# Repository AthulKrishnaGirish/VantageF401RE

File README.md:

# VantageF401RE

### STM32F401RE Evaluation & Development Board

**Mixed Traces PCB Design Competition — 2026  —**
**Submission by, Athul Krishna Girish**

---

## Project Overview

**VantageF401RE** is an independently designed, compact **2-layer STM32F401RE-based evaluation and development board** developed in KiCad as part of the **Mixed Traces PCB Design Competition 2026**.

The board is built around the **STM32F401RET6** microcontroller and integrates the essential features expected from a development board, including regulated power, USB connectivity, SWD programming/debugging, UART, SPI, I²C, GPIO expansion, reset and boot control, user indicators, and supporting protection and decoupling circuitry.

The design was developed independently with the **STM32 NUCLEO-F401RE** used as a functional and architectural reference. The VantageF401RE schematic, component arrangement, PCB placement, and routing were independently developed and are not a direct copy of the NUCLEO PCB layout.

---

## Project Status

### Completed — Final Design

The VantageF401RE schematic and PCB layout have been completed in KiCad.

The project includes:

- Complete STM32F401RET6-based schematic
- Power supply and 3.3 V regulation
- USB-C power and USB 2.0 interface
- USB ESD protection
- SWD programming/debugging interface
- UART interface
- SPI interface
- I²C interface
- GPIO expansion
- Reset and BOOT selection circuitry
- User button and LED
- Power and USB status indicators
- External 5 V input
- Crystal oscillator
- MCU power decoupling
- Test points
- Two-layer PCB layout
- Ground copper zones
- ERC and DRC verification
- Final Gerber and drill file generation
- Final component list and design documentation

The final PCB design achieved **0 reported DRC errors**, and the final manufacturing files were generated from the completed PCB layout.

> **Note:** The project was developed and verified as a PCB design in KiCad. No physical fabrication or hardware testing is claimed as part of this submission.

---

## Key Specifications

| Parameter | Specification |
|---|---|
| **Board Name** | VantageF401RE |
| **MCU** | STM32F401RET6 |
| **MCU Package** | LQFP-64 |
| **PCB Layers** | 2 copper layers |
| **PCB Dimensions** | 80 mm × 60 mm |
| **Design Software** | KiCad |
| **Logic Supply** | 3.3 V |
| **USB Interface** | USB Type-C / USB 2.0 |
| **Programming & Debugging** | SWD |
| **Communication Interfaces** | UART, SPI, I²C |
| **GPIO Expansion** | 20-pin header |
| **External Power** | 5 V input |
| **PCB Verification** | ERC / DRC |
| **Fabrication Requirement** | Not required |

---

## Main Features

### 1. STM32F401RET6 Core

The board uses the **STM32F401RET6**, a 64-pin LQFP STM32F4-series microcontroller.

The MCU section includes:

- 3.3 V digital supply
- Analog supply connection
- VCAP capacitor
- Local decoupling capacitors
- External HSE crystal
- Reset circuitry
- BOOT0 configuration
- SWD programming/debugging access

---

### 2. Power Supply

The board provides a regulated **3.3 V supply** for the STM32F401RET6 and peripheral circuitry.

**Power inputs**

- USB-C 5 V input
- External 5 V input

**Regulation**

An **AP2112K-3.3 LDO regulator** converts the incoming 5 V supply to 3.3 V.

The power section includes:

- Input decoupling
- Output decoupling
- 3.3 V bulk capacitance
- Power indication
- External-input protection

An **SS14 Schottky diode** is included on the external 5 V input path for protection.

---

### 3. USB-C Interface

The board provides a USB Type-C connector for power and USB 2.0 data connectivity.

The USB section includes:

- USB-C receptacle
- USB 2.0 D+ and D− connections
- CC1 and CC2 configuration resistors
- USB ESD protection
- USB D+ and D− series resistors
- USB status indicator

The USB data path uses the STM32F401RE USB pins:

- **PA11 — USB_DM**
- **PA12 — USB_DP**

---

### 4. USB ESD Protection

A **USBLC6-2SC6** protection device is placed close to the USB connector.

The protection network is incorporated into the USB data path to provide ESD protection for the USB D+ and D− lines.

The USB signal path is organized as:

```text
USB-C
  ↓
USB D+ / D−
  ↓
USB ESD Protection
  ↓
22 Ω Series Resistors
  ↓
STM32F401RET6
```

---

### 5. SWD Programming & Debugging

A dedicated 5-pin SWD header is provided for programming and debugging the STM32F401RET6.

The interface provides:

- VCC
- SWDIO
- GND
- SWCLK
- NRST

MCU connections:

- PA13 — SWDIO
- PA14 — SWCLK
- NRST — Reset

Dedicated test points are also provided for SWDIO, SWCLK, and NRST.

---

### 6. UART Interface

A dedicated 4-pin UART header provides easy access to the serial communication interface.

| UART Signal | MCU Pin |
|---|---|
| UART_TX | PA2 |
| UART_RX | PA3 |
| VCC | +3V3 |
| GND | GND |

---

### 7. SPI Interface

A dedicated 6-pin SPI header is provided.

| SPI Signal | MCU Pin |
|---|---|
| SPI_SCK | PA5 |
| SPI_MISO | PA6 |
| SPI_MOSI | PA7 |
| SPI_CS | PA4 |
| VCC | +3V3 |
| GND | GND |

---

### 8. I²C Interface

A dedicated 4-pin I²C header is provided with external pull-up resistors.

| I²C Signal | MCU Pin |
|---|---|
| I2C_SCL | PB6 |
| I2C_SDA | PB7 |
| VCC | +3V3 |
| GND | GND |

Two 4.7 kΩ pull-up resistors are provided for the I²C lines.

---

### 9. GPIO Expansion

A dedicated 20-pin GPIO expansion header provides access to multiple STM32 GPIOs along with power and ground.

The expansion header provides access to signals including:

- PA0
- PA1
- PA8
- PA9
- PA10
- PB2
- PB10
- PC6
- PB12–PB15
- PC0–PC5
- +3V3
- GND

This provides flexibility for connecting external sensors, modules, displays, and other peripherals.

---

### 10. Reset & Boot Control

**Reset**

The NRST line includes:

- 10 kΩ pull-up resistor
- Dedicated reset pushbutton
- SWD NRST connection
- NRST test point

**Boot Selection**

BOOT0 includes:

- 10 kΩ pull-down resistor
- Dedicated BOOT selection header
- +3V3 selection capability

This allows the boot configuration of the STM32F401RET6 to be conveniently controlled.

---

## User Interface

The board includes dedicated user indicators and controls.

**User LED**

- D1 — USER_LED
- Controlled through PB0
- R3 = 330 Ω current-limiting resistor

**User Button**

- SW2 — USER_BTN
- Connected to PB1
- R4 = 10 kΩ pull-up resistor

**Power LED**

- D2 — POWER
- R9 = 1 kΩ current-limiting resistor

**USB Status LED**

- D4 — USB_STATUS
- Controlled through PB5
- R12 = 1 kΩ current-limiting resistor

---

## Clock Circuit

The MCU uses an external 8 MHz HSE crystal.

The clock section consists of:

- Y1 — 8 MHz crystal
- C2 — 18 pF
- C3 — 18 pF

The crystal and its load capacitors are placed close to the MCU to maintain a compact and controlled clock path.

---

## Decoupling & Power Integrity

Local decoupling is provided around the STM32F401RET6 and the power-supply circuitry.

The design includes:

- VDD decoupling capacitors
- VCAP capacitor
- Analog supply decoupling
- 3.3 V bulk capacitance
- LDO input and output capacitors

The final PCB placement keeps critical decoupling components close to their respective power pins and maintains short power/ground paths.

---

## PCB Design

The VantageF401RE PCB was designed as a two-layer board while maintaining the competition's maximum board-size requirement.

**Final board dimensions:** 80 mm × 60 mm

**PCB design considerations**

- Central MCU placement
- Short critical signal paths
- Dedicated power section
- USB connector at the board edge
- Accessible programming/debugging header
- Clearly grouped communication headers
- GPIO expansion access
- Local MCU decoupling
- Ground copper zones
- Organized component placement
- Practical connector accessibility
- Compact routing while maintaining design-rule compliance

The PCB layout was independently developed rather than directly reproducing the NUCLEO-F401RE PCB layout.

---

## Final Component Set

The completed design contains 47 populated component references:

| Category | Quantity |
|---|---|
| MCU | 1 |
| USB Protection | 1 |
| Voltage Regulator | 1 |
| Connectors | 8 |
| Crystal | 1 |
| Resistors | 12 |
| Capacitors | 12 |
| LEDs | 3 |
| Diode | 1 |
| Switches | 2 |
| Test Points | 5 |
| **Total** | **47** |

The complete component list is available in:
`bom/VantageF401RE_Final_Component_List.xlsx`

The component reference designators in the final documentation follow the final schematic.

---

## Verification

The design was checked using KiCad's electrical and physical design-rule verification tools.

**ERC — Electrical Rules Check**

- 0 violations
- 0 errors
- 0 warnings

**DRC — Design Rules Check**

- 0 reported DRC errors

The final Gerber and drill files were generated from the completed PCB layout after routing and design-rule verification.

---

## Repository Contents

The repository contains the complete design and supporting documentation.

```text
VantageF401RE/
│
├── bom/
│   └── VantageF401RE_Final_Component_List.xlsx
│
├── docs/
│   ├── Major Decisions.md
│   └── Initial Block Diagram.png
│
├── gerbers/
│   ├── VantageF401RE_Gerbers.zip
│   └── README.md
│
├── kicad/
│   ├── VantageF401RE.kicad_sch
│   ├── VantageF401RE.kicad_pcb
│   ├── VantageF401RE.kicad_pro
│   └── README.md
│
├── pdf/
│   ├── VantageF401RE_Final_Design_Report.pdf
│   └── README.md
│
├── results/
│   ├── ERC / DRC and validation results
│   └── README.md
│
└── README.md
```

---

### Folder Description

| [`bom/`](bom/) |
Contains the final component list and BOM-related documentation.
`VantageF401RE_Final_Component_List.xlsx` — provides the final component references, values, footprints, functions, and interface mapping.

| [`docs/`](docs/) |
Contains supporting project documentation, design information, and technical documentation associated with the development of the board.

| [`gerbers/`](gerbers/) |
Contains the final manufacturing output package.
`VantageF401RE_Gerbers.zip` — includes the final copper, solder-mask, silkscreen, paste, board-outline, and drill outputs generated from KiCad.

| [`kicad/`](kicad/) |
Contains the primary editable KiCad design files, including:

- Schematic
- PCB layout
- Supporting KiCad project files

These files represent the actual circuit and PCB implementation of VantageF401RE.

| [`pdf/`](pdf/) |
Contains the final technical design report prepared for the competition submission.
`VantageF401RE_Final_Design_Report.pdf` — provides a consolidated description of the board architecture, design decisions, implementation, verification, and final outcome.

| [`results/`](results/) |
Contains design verification and validation outputs, including ERC/DRC-related results and other relevant design-check documentation.

---

## Competition Compliance

| Requirement | VantageF401RE |
|---|---|
| STM32F401RE MCU | ✓ |
| Maximum 100 mm × 100 mm | ✓ |
| Exactly 2 copper layers | ✓ |
| Power input | ✓ |
| Voltage regulation | ✓ |
| Decoupling | ✓ |
| Power indication | ✓ |
| SWD interface | ✓ |
| Reset button | ✓ |
| User button | ✓ |
| User LED | ✓ |
| UART | ✓ |
| SPI | ✓ |
| I²C | ✓ |
| GPIO expansion | ✓ |
| USB interface | ✓ |
| ERC verification | ✓ |
| DRC verification | ✓ |
| Gerber generation | ✓ |
| Final BOM | ✓ |
| Technical documentation | ✓ |

---

## Design Philosophy

The VantageF401RE was designed with the following priorities:

- Electrical correctness
- Reliable power distribution
- Practical peripheral access
- Compact PCB organization
- Clear interface grouping
- Debugging accessibility
- Protection and robustness
- Expandability
- Manufacturing-oriented PCB design
- Clean and structured documentation

The design balances the requirements of a development board with the constraints of a compact two-layer PCB.

---

## Final Outcome

The VantageF401RE project progressed from initial architecture and component planning to a completed schematic, PCB layout, verification, and manufacturing-output generation.

The final repository provides the editable KiCad design files together with the final component list, verification results, Gerber package, and technical design report.

The result is a compact, independently developed STM32F401RE evaluation and development board intended to provide convenient access to programming, debugging, communication, GPIO expansion, USB connectivity, and basic user-interface functionality.

---

## Project Information

- **Project:** VantageF401RE
- **Board:** STM32F401RE Evaluation & Development Board
- **Competition:** Mixed Traces PCB Design Competition — 2026
- **Organizer:** Mixed Signals — Electronics Association of MEC
- **Design Tool:** KiCad
- **MCU:** STM32F401RET6
- **PCB:** 2-layer, 80 mm × 60 mm

---

## Acknowledgement

Developed as a submission for the Mixed Traces PCB Design Competition 2026, organized by Mixed Signals — Electronics Association of MEC.

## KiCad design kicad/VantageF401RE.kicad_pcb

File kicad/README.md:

# VantageF401RE — KiCad Design Files

This folder contains the complete editable **KiCad project files** for the **VantageF401RE**, a custom STM32F401RE-based evaluation and development board designed for the **Mixed Traces PCB Design Competition** by Mixed Signals, Electronics Association of MEC.

The design was developed entirely in **KiCad** as a **2-layer PCB**, with a focus on functionality, accessibility, protection, compact organization, and practical embedded-system development.

---

## Project Files

| File | Description |
|------|-------------|
| `VantageF401RE.kicad_pro` | Main KiCad project file |
| `VantageF401RE.kicad_sch` | Complete electrical schematic |
| `VantageF401RE.kicad_pcb` | Final 2-layer PCB layout |

These files can be opened and edited using KiCad.

---

## Board Specifications

| Parameter | Specification |
|-----------|---------------|
| MCU | STM32F401RET6 |
| MCU Package | LQFP-64 |
| PCB Layers | 2 |
| Board Size | 80 mm × 60 mm |
| Design Tool | KiCad |
| USB Interface | USB Type-C, USB 2.0 |
| Supply Voltage | 3.3 V regulated |
| External Input | 5 V |
| Debug Interface | SWD |
| Oscillator | 8 MHz external crystal |

The board size remains well within the competition's maximum permitted **100 mm × 100 mm** area.

---

## Main Functional Blocks

The VantageF401RE integrates the following functional sections:

### 1. STM32F401RET6 Core

The STM32F401RET6 serves as the main processing device.

The design includes:

- External 8 MHz crystal oscillator
- VCAP1 capacitor
- MCU power decoupling
- Analog supply decoupling
- Reset circuitry
- BOOT0 configuration
- Dedicated programming/debug access

---

### 2. Power Management

The power section provides a regulated 3.3 V supply for the MCU and peripherals.

Features include:

- USB-C 5 V input
- External 5 V input
- AP2112K-3.3 LDO regulator
- Input and output capacitors
- Schottky-diode protection for external 5 V input
- Power LED
- 3.3 V and GND test points

---

### 3. USB Interface

A USB-C connector is provided for USB 2.0 connectivity and 5 V power input.

The USB section includes:

- USB Type-C receptacle
- USB D+ and D− connections
- CC1 and CC2 resistors
- USB ESD protection using USBLC6-2SC6
- USB data-line series resistors
- USB status LED
- Dedicated USB 5 V power rail

The USB data path is protected before reaching the STM32 USB pins.

---

### 4. SWD Programming and Debugging

A dedicated 5-pin SWD header is provided for programming and debugging the STM32.

The interface exposes:

- VCC
- SWDIO
- GND
- SWCLK
- NRST

Test points are also provided for SWDIO, SWCLK, and NRST.

---

### 5. Reset and Boot Configuration

The board provides dedicated controls for reliable startup and debugging.

Features include:

- Hardware reset push button
- NRST pull-up resistor
- BOOT0 pull-down resistor
- BOOT selection header

---

### 6. Communication Interfaces

Dedicated headers are provided for commonly used embedded communication protocols.

#### UART

- UART TX
- UART RX
- 3.3 V
- GND

#### SPI

- SPI SCK
- SPI MISO
- SPI MOSI
- SPI CS
- 3.3 V
- GND

#### I²C

- I²C SCL
- I²C SDA
- 3.3 V
- GND
- Dedicated pull-up resistors

---

### 7. GPIO Expansion

A dedicated **2×10 GPIO header** provides convenient access to multiple STM32 GPIO pins along with power and ground connections.

This allows external sensors, displays, modules, and other peripherals to be connected directly to the board.

---

### 8. User Interface

The board includes:

- User push button
- User LED
- Reset button
- Power LED
- USB status LED
- BOOT selection header

These provide basic interaction and visual feedback during development and debugging.

---

### 9. Clock and Decoupling

The MCU clock section uses an external **8 MHz crystal oscillator** with dedicated load capacitors.

The power network includes:

- Local 100 nF MCU decoupling capacitors
- Bulk 4.7 µF decoupling
- Analog supply filtering
- VCAP1 capacitor
- Regulator input/output capacitors

The decoupling components were placed close to their respective power pins and functional blocks during PCB layout.

---

### 10. Test and Debug Access

Dedicated test points are provided for important signals:

- 3.3 V
- GND
- SWDIO
- SWCLK
- NRST

These improve accessibility for oscilloscope probing, debugging, and laboratory measurements.

---

## PCB Layout

The final PCB uses a **2-layer copper stack-up** with an **80 mm × 60 mm** board outline.

The placement was organized into functional regions, including:

- Central STM32 MCU section
- USB and power section near the board edge
- SWD/debug section
- Communication interface headers
- GPIO expansion
- Clock circuitry
- User-control section
- Power indication
- Test points

Ground planes are used to provide continuous ground-return paths and improve overall PCB organization.

The layout was routed while considering component accessibility, signal paths, power distribution, and the physical constraints of a 2-layer board.

---

## Design Verification

The final schematic and PCB were verified using KiCad's electrical and PCB design-rule checking tools.

### ERC

**Electrical Rules Check:**

- Violations: **0**
- Errors: **0**
- Warnings: **0**

### DRC

**Design Rules Check:**

- Reported violations: **0**
- Errors: **0**
- Intentional exclusions: **4**

The intentional exclusions correspond to reviewed USB-C connector mechanical hole-clearance checks associated with the selected footprint.

Detailed ERC and DRC reports are available in the repository's [`results/`](../results/) directory.

---

## Design Approach

The VantageF401RE was designed as a complete development platform rather than only an STM32 breakout board.

The design combines:

**Processing + Power + USB + Debugging + Communication + Expansion + User Interface + Protection**

within a compact 2-layer PCB.

Particular attention was given to:

- Power integrity
- Local decoupling
- USB protection
- Signal accessibility
- Debug accessibility
- Peripheral expansion
- Component placement
- Ground connectivity
- PCB manufacturability
- Design-rule compliance

---

## Related Repository Folders

The complete project is organized into dedicated sections:

### [`bom/`](../bom/)

Contains the component selection and BOM documentation.

### [`docs/`](../docs/)

Contains project documentation, including:

- Major design decisions
- Initial block diagram
- Progress evaluation documentation

### [`results/`](../results/)

Contains the final ERC and DRC verification reports.

### [`gerbers/`](../gerbers/)

Contains the final Gerber and drill files prepared for PCB fabrication.

### [`pdf/`](../pdf/)

Reserved for the final project documentation PDF.

---

## Opening the Project

To inspect or continue development:

1. Install a compatible version of KiCad.
2. Open `VantageF401RE.kicad_pro`.
3. Open the schematic through the KiCad project manager.
4. Open the PCB layout from the same project.

The `.kicad_sch` and `.kicad_pcb` files can also be opened individually when required.

---

## Final Design Status

The VantageF401RE design has completed:

- Component selection
- Schematic development
- PCB component placement
- PCB routing
- Power-system implementation
- USB interface implementation
- SWD interface implementation
- UART, SPI and I²C interfaces
- GPIO expansion
- User interface circuitry
- PCB design-rule verification
- Schematic electrical-rule verification
- Gerber and drill-file generation

The files in this directory represent the **final editable KiCad design** submitted as part of the project.

---

**Project:** VantageF401RE  
**MCU:** STM32F401RET6  
**PCB:** 2-Layer, 80 mm × 60 mm  
**EDA Tool:** KiCad  
**Status:** Final Design Completed

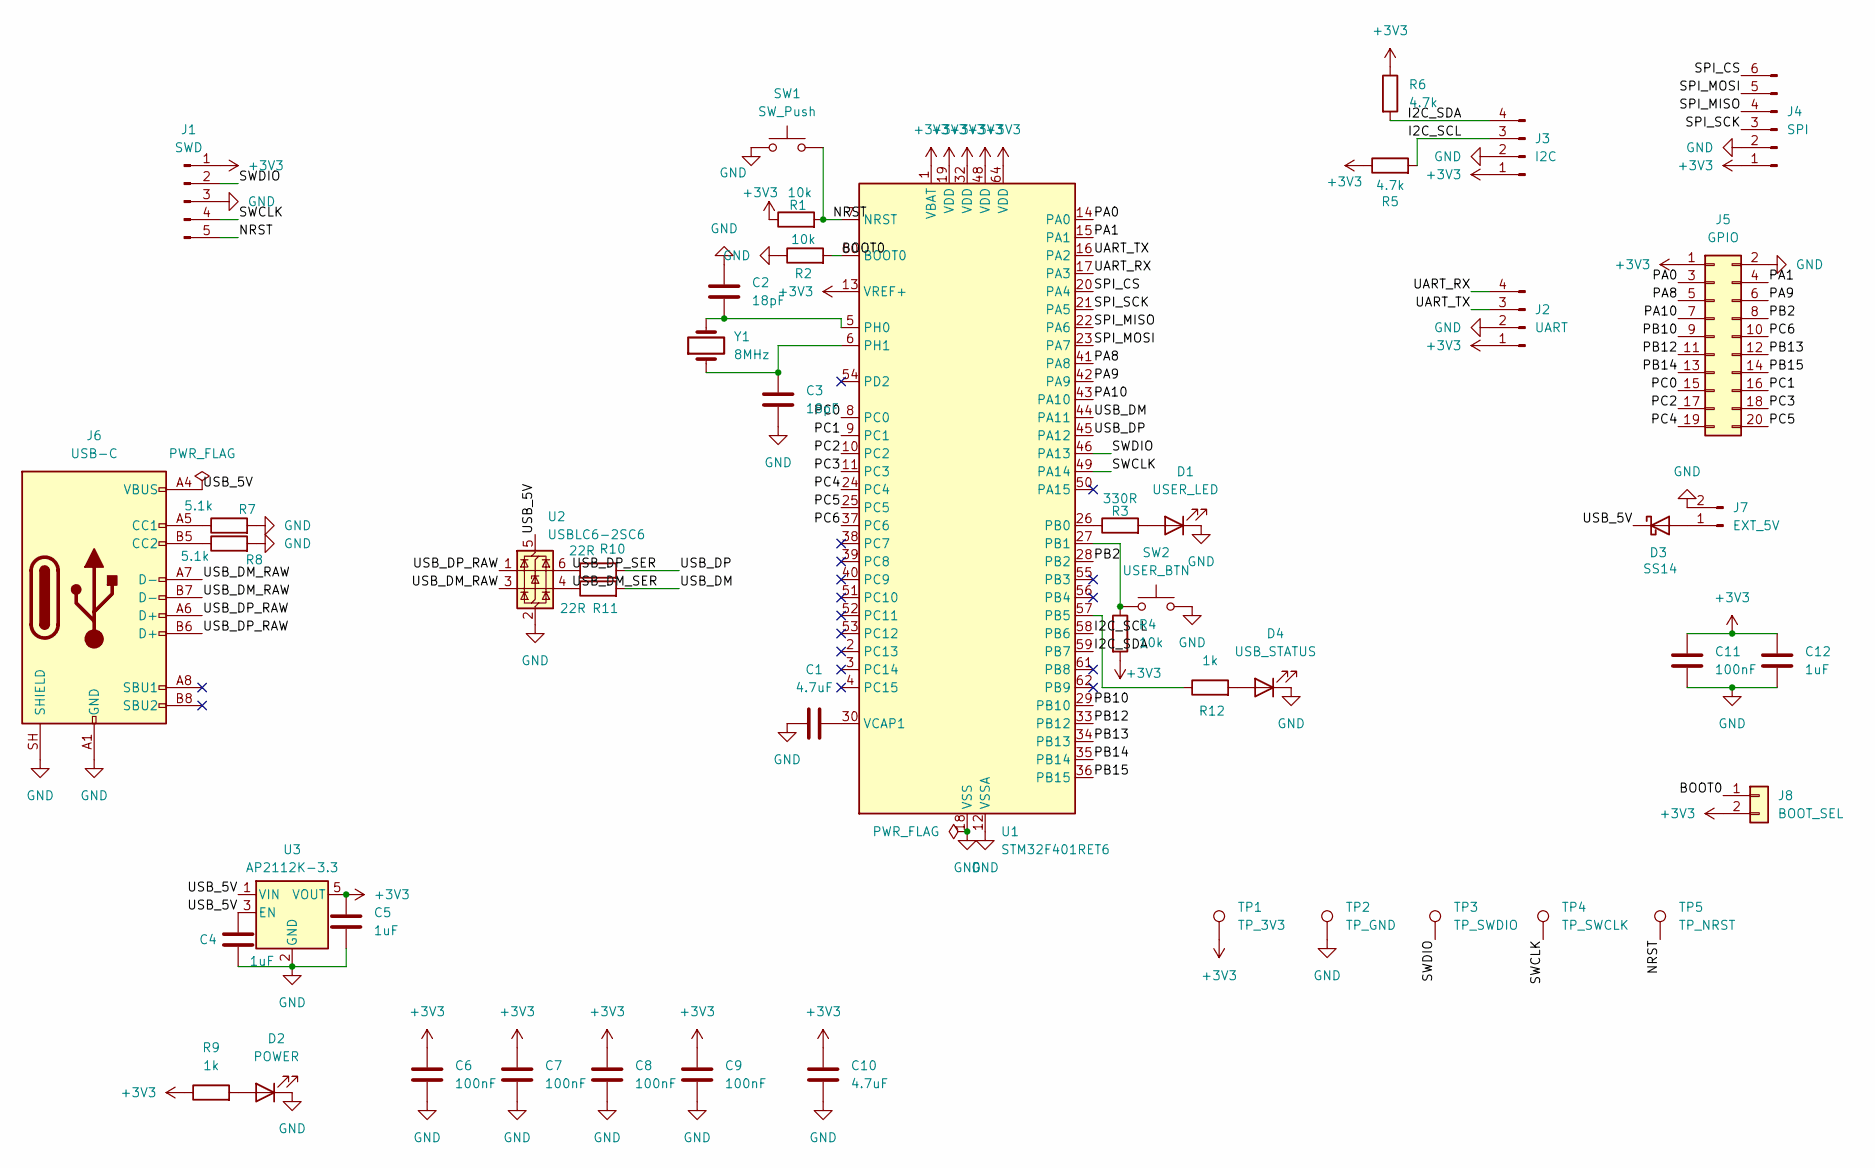
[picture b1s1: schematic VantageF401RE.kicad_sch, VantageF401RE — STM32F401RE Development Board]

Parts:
C1, C10: 4.7uF; C_0805_2012Metric
C2, C3: 18pF; C_0805_2012Metric
C4, C5, C12: 1uF; C_0805_2012Metric
C6, C7, C8, C9, C11: 100nF; C_0805_2012Metric
D1: USER_LED; LED_0805_2012Metric
D2: POWER; LED_0805_2012Metric
D3: SS14; D_SMA
D4: USB_STATUS; LED_0805_2012Metric
J1: SWD; PinHeader_1x05_P2.54mm_Vertical
J2: UART; PinHeader_1x04_P2.54mm_Vertical
J3: I2C; PinHeader_1x04_P2.54mm_Vertical
J4: SPI; PinHeader_1x06_P2.54mm_Vertical
J5: GPIO; PinHeader_2x10_P2.54mm_Vertical
J6: USB-C; USB_C_Receptacle_GCT_USB4105-xx-A_16P_TopMnt_Horizontal
J7: EXT_5V; PinHeader_1x02_P2.54mm_Vertical
J8: BOOT_SEL; PinHeader_1x02_P2.54mm_Vertical
R1, R2, R4: 10k; R_0805_2012Metric
R3: 330R; R_0805_2012Metric
R5, R6: 4.7k; R_0805_2012Metric
R7, R8: 5.1k; R_0805_2012Metric
R9, R12: 1k; R_0805_2012Metric
R10, R11: 22R; R_0805_2012Metric
SW1: SW_Push; SW_PUSH_6mm
SW2: USER_BTN; SW_PUSH_6mm
TP1: TP_3V3; TestPoint_Plated_Hole_D2.0mm
TP2: TP_GND; TestPoint_Plated_Hole_D2.0mm
TP3: TP_SWDIO; TestPoint_Plated_Hole_D2.0mm
TP4: TP_SWCLK; TestPoint_Plated_Hole_D2.0mm
TP5: TP_NRST; TestPoint_Plated_Hole_D2.0mm
U1: STM32F401RET6; LQFP-64_10x10mm_P0.5mm
U2: USBLC6-2SC6; SOT-23-6
U3: AP2112K-3.3; SOT-23-5
Y1: 8MHz; Crystal_SMD_3225-4Pin_3.2x2.5mm

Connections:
+3V3: C5.1, C6.1, C7.1, C8.1, C9.1, C10.1, C11.1, C12.1, J1.1, J2.1, J3.1, J4.1, J5.1, J8.2, R1.1, R4.2, R5.1, R6.1, R9.1, TP1.1 (1_1), U1.1 (VBAT), U1.13 (VREF+), U1.19 (VDD), U1.32 (VDD), U1.48 (VDD), U1.64 (VDD), U3.5 (VOUT)
/BOOT0: J8.1, R2.2, U1.60 (BOOT0)
/I2C_SCL: J3.3, R5.2, U1.58 (PB6)
/I2C_SDA: J3.4, R6.2, U1.59 (PB7)
/NRST: J1.5, R1.2, SW1.2, TP5.1 (1_1), U1.7 (NRST)
/PA0: J5.3, U1.14 (PA0)
/PA1: J5.4, U1.15 (PA1)
/PA8: J5.5, U1.41 (PA8)
/PA9: J5.6, U1.42 (PA9)
/PA10: J5.7, U1.43 (PA10)
/PB2: J5.8, U1.28 (PB2)
/PB10: J5.9, U1.29 (PB10)
/PB12: J5.11, U1.33 (PB12)
/PB13: J5.12, U1.34 (PB13)
/PB14: J5.13, U1.35 (PB14)
/PB15: J5.14, U1.36 (PB15)
/PC0: J5.15, U1.8 (PC0)
/PC1: J5.16, U1.9 (PC1)
/PC2: J5.17, U1.10 (PC2)
/PC3: J5.18, U1.11 (PC3)
/PC4: J5.19, U1.24 (PC4)
/PC5: J5.20, U1.25 (PC5)
/PC6: J5.10, U1.37 (PC6)
/SPI_CS: J4.6, U1.20 (PA4)
/SPI_MISO: J4.4, U1.22 (PA6)
/SPI_MOSI: J4.5, U1.23 (PA7)
/SPI_SCK: J4.3, U1.21 (PA5)
/SWCLK: J1.4, TP4.1 (1_1), U1.49 (PA14)
/SWDIO: J1.2, TP3.1 (1_1), U1.46 (PA13)
/UART_RX: J2.4, U1.17 (PA3)
/UART_TX: J2.3, U1.16 (PA2)
/USB_5V: C4.1, D3.1 (K), J6.A4 (VBUS), J6.A9 (VBUS), J6.B4 (VBUS), J6.B9 (VBUS), U2.5 (VBUS), U3.1 (VIN), U3.3 (EN)
/USB_DM: R11.2, U1.44 (PA11)
/USB_DM_RAW: J6.A7 (D-), J6.B7 (D-), U2.3 (I/O2)
/USB_DM_SER: R11.1, U2.4 (I/O2)
/USB_DP: R10.2, U1.45 (PA12)
/USB_DP_RAW: J6.A6 (D+), J6.B6 (D+), U2.1 (I/O1)
/USB_DP_SER: R10.1, U2.6 (I/O1)
GND: C1.1, C2.1, C3.2, C4.2, C5.2, C6.2, C7.2, C8.2, C9.2, C10.2, C11.2, C12.2, D1.1 (K), D2.1 (K), D4.1 (K), J1.3, J2.2, J3.2, J4.2, J5.2, J6.A1 (GND), J6.A12 (GND), J6.B1 (GND), J6.B12 (GND), J6.SH (SHIELD), J7.2, R2.1, R7.2, R8.2, SW1.1, SW2.2, TP2.1 (1_1), U1.12 (VSSA), U1.18 (VSS), U1.31 (VSS), U1.47 (VSS), U1.63 (VSS), U2.2 (GND), U3.2 (GND)
unnamed: D1.2 (A), R3.2
unnamed: D2.2 (A), R9.2
unnamed: D3.2 (A), J7.1
unnamed: D4.2 (A), R12.2
unnamed: J6.A5 (CC1), R7.1
unnamed: J6.B5 (CC2), R8.1
unnamed: R3.1, U1.26 (PB0)
unnamed: R4.1, SW2.1, U1.27 (PB1)
unnamed: R12.1, U1.57 (PB5)
unnamed: C2.2, U1.5 (PH0), Y1.2
unnamed: C3.1, U1.6 (PH1), Y1.1
unnamed: C1.2, U1.30 (VCAP1)

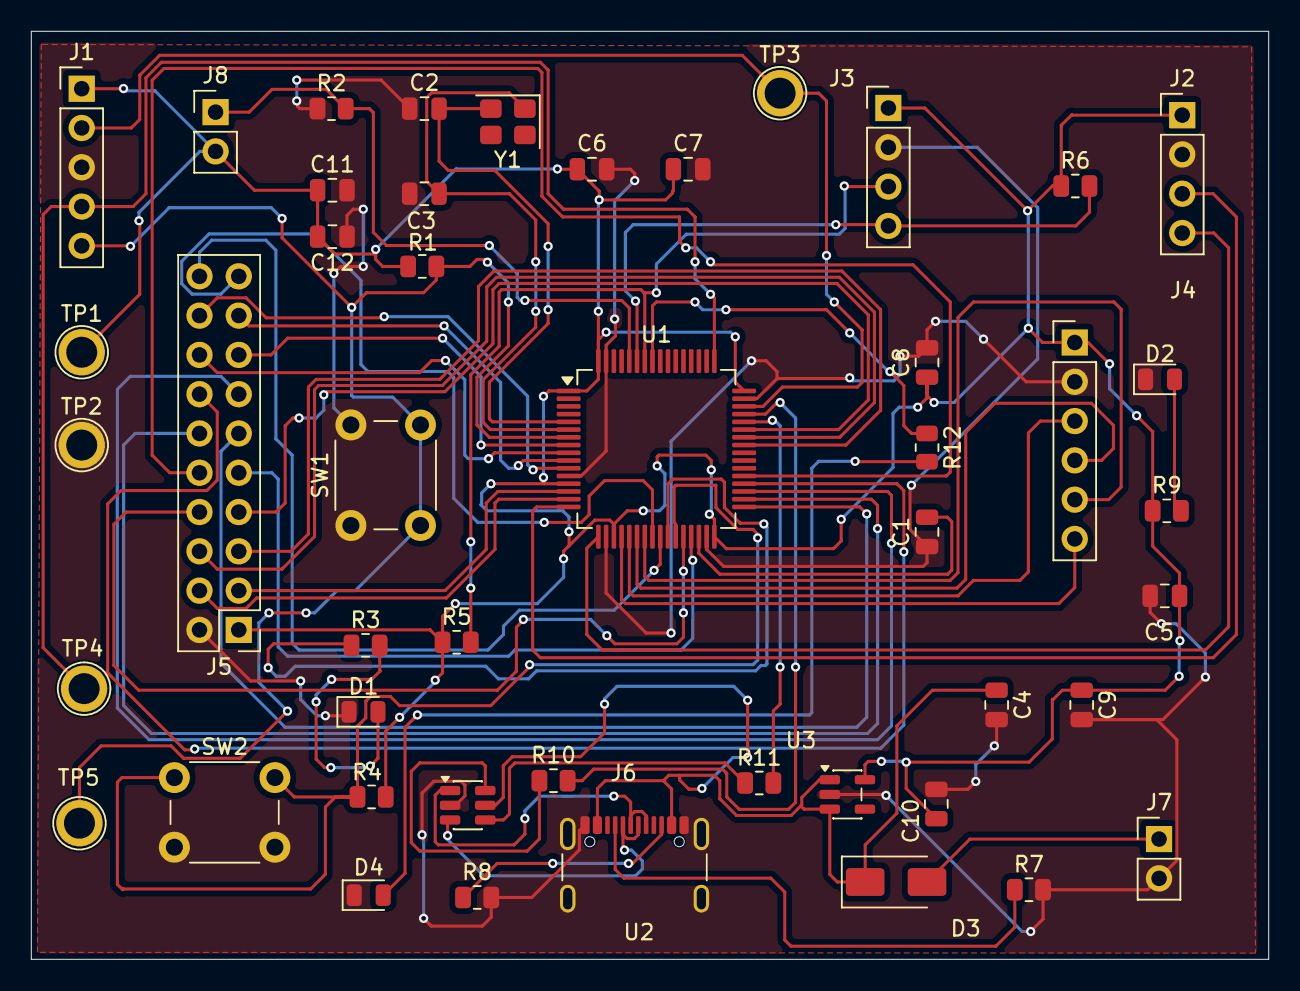
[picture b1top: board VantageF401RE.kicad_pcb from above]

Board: 2 copper layers, 80.0 x 60.0 mm, 47 parts (0 on the bottom side), 51 nets.

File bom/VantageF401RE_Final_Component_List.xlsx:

VantageF401RE — Final Component List / BOM
Authoritative source: supplied final KiCad schematic screenshots
PCB: 2-layer, 80 mm × 60 mm | MCU: STM32F401RET6 | Total populated references: 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
Reference | Category | Value / Part | Footprint | Qty | Function | Notes
U1 | MCU | STM32F401RET6 | Package_QFP:LQFP-64_10x10mm_P0.5mm | 1 | Main microcontroller | STM32F401RETx symbol; 64-pin LQFP
U2 | USB Protection | USBLC6-2SC6 | Package_TO_SOT_SMD:SOT-23-6 | 1 | USB ESD protection | USB 2.0 D+/D- protection
U3 | Voltage Regulator | AP2112K-3.3 | Package_TO_SOT_SMD:SOT-23-5 | 1 | 3.3 V LDO regulator | USB_5V to +3V3
J1 | Connector | SWD | Connector_PinHeader_2.54mm:PinHeader_1x05_P2.54mm_Vertical | 1 | SWD programming/debug | VCC, SWDIO, GND, SWCLK, NRST
J2 | Connector | UART | Connector_PinHeader_2.54mm:PinHeader_1x04_P2.54mm_Vertical | 1 | UART expansion | +3V3, GND, TX, RX
J3 | Connector | I2C | Connector_PinHeader_2.54mm:PinHeader_1x04_P2.54mm_Vertical | 1 | I²C expansion | +3V3, GND, SCL, SDA
J4 | Connector | SPI | Connector_PinHeader_2.54mm:PinHeader_1x06_P2.54mm_Vertical | 1 | SPI expansion | +3V3, GND, SCK, MISO, MOSI, CS
J5 | Connector | GPIO | Connector_PinHeader_2.54mm:PinHeader_2x10_P2.54mm_Vertical | 1 | GPIO expansion | 20-pin header
J6 | Connector | USB-C | Connector_USB:USB_C_Receptacle_GCT_USB4105-xx-A_16P_TopMnt_Horizontal | 1 | USB power/data | USB 2.0 Type-C receptacle
J7 | Connector | EXT_5V | Connector_PinHeader_2.54mm:PinHeader_1x02_P2.54mm_Vertical | 1 | External 5 V input | Protected by SS14
J8 | Connector | BOOT_SEL | Connector_PinHeader_2.54mm:PinHeader_1x02_P2.54mm_Vertical | 1 | Boot-mode selection | BOOT0 to +3V3 jumper
Y1 | Crystal | 8MHz | Crystal:Crystal_SMD_3225-4Pin_3.2x2.5mm | 1 | High-speed external oscillator | HSE crystal
R1 | Resistor | 10kΩ | Resistor_SMD:R_0805_2012Metric | 1 | NRST pull-up | +3V3 to NRST
R2 | Resistor | 10kΩ | Resistor_SMD:R_0805_2012Metric | 1 | BOOT0 pull-down | BOOT0 to GND
R3 | Resistor | 330Ω | Resistor_SMD:R_0805_2012Metric | 1 | User LED current limiting | PB0 to D1
R4 | Resistor | 10kΩ | Resistor_SMD:R_0805_2012Metric | 1 | User button pull-up | PB1 to +3V3
R5 | Resistor | 4.7kΩ | Resistor_SMD:R_0805_2012Metric | 1 | I²C SCL pull-up | +3V3 to I2C_SCL
R6 | Resistor | 4.7kΩ | Resistor_SMD:R_0805_2012Metric | 1 | I²C SDA pull-up | +3V3 to I2C_SDA
R7 | Resistor | 5.1kΩ | Resistor_SMD:R_0805_2012Metric | 1 | USB-C CC1 pull-down | CC1 to GND
R8 | Resistor | 5.1kΩ | Resistor_SMD:R_0805_2012Metric | 1 | USB-C CC2 pull-down | CC2 to GND
R9 | Resistor | 1kΩ | Resistor_SMD:R_0805_2012Metric | 1 | Power LED current limiting | +3V3 to D2
R10 | Resistor | 22Ω | Resistor_SMD:R_0805_2012Metric | 1 | USB D+ series resistor | USB_DP_SER to USB_DP
R11 | Resistor | 22Ω | Resistor_SMD:R_0805_2012Metric | 1 | USB D− series resistor | USB_DM_SER to USB_DM
R12 | Resistor | 1kΩ | Resistor_SMD:R_0805_2012Metric | 1 | USB status LED current limiting | PB5 to D4
C1 | Capacitor | 4.7µF | Capacitor_SMD:C_0805_2012Metric | 1 | VCAP1 capacitor | VCAP1 to GND
C2 | Capacitor | 18pF | Capacitor_SMD:C_0805_2012Metric | 1 | HSE load capacitor | PH0 side to GND
C3 | Capacitor | 18pF | Capacitor_SMD:C_0805_2012Metric | 1 | HSE load capacitor | PH1 side to GND
C4 | Capacitor | 1µF | Capacitor_SMD:C_0805_2012Metric | 1 | LDO input decoupling | USB_5V to GND
C5 | Capacitor | 1µF | Capacitor_SMD:C_0805_2012Metric | 1 | LDO output decoupling | +3V3 to GND
C6 | Capacitor | 100nF | Capacitor_SMD:C_0805_2012Metric | 1 | MCU VDD decoupling | +3V3 to GND
C7 | Capacitor | 100nF | Capacitor_SMD:C_0805_2012Metric | 1 | MCU VDD decoupling | +3V3 to GND
C8 | Capacitor | 100nF | Capacitor_SMD:C_0805_2012Metric | 1 | MCU VDD decoupling | +3V3 to GND
C9 | Capacitor | 100nF | Capacitor_SMD:C_0805_2012Metric | 1 | MCU VDD decoupling | +3V3 to GND
C10 | Capacitor | 4.7µF | Capacitor_SMD:C_0805_2012Metric | 1 | Bulk 3.3 V decoupling | +3V3 to GND
C11 | Capacitor | 100nF | Capacitor_SMD:C_0805_2012Metric | 1 | Analog supply decoupling | VDDA/VREF+ supply
C12 | Capacitor | 1µF | Capacitor_SMD:C_0805_2012Metric | 1 | Analog supply decoupling | VDDA/VREF+ supply
D1 | LED | USER_LED | LED_SMD:LED_0805_2012Metric | 1 | User indicator | Driven by PB0
D2 | LED | POWER | LED_SMD:LED_0805_2012Metric | 1 | 3.3 V power indicator | On when +3V3 is present
D3 | Diode | SS14 | Diode_SMD:D_SMA | 1 | External 5 V reverse-polarity protection | EXT_5V to USB_5V
D4 | LED | USB_STATUS | LED_SMD:LED_0805_2012Metric | 1 | USB/status indicator | Driven by PB5
SW1 | Switch | SW_Push | Button_Switch_THT:SW_PUSH_6mm | 1 | Reset button | NRST to GND
SW2 | Switch | USER_BTN | Button_Switch_THT:SW_PUSH_6mm | 1 | User button | PB1 to GND
TP1 | Test Point | TP_3V3 | TestPoint:TestPoint_Plated_Hole_D2.0mm | 1 | 3.3 V test point | +3V3
TP2 | Test Point | TP_GND | TestPoint:TestPoint_Plated_Hole_D2.0mm | 1 | Ground test point | GND
TP3 | Test Point | TP_SWDIO | TestPoint:TestPoint_Plated_Hole_D2.0mm | 1 | SWDIO test point | SWDIO
TP4 | Test Point | TP_SWCLK | TestPoint:TestPoint_Plated_Hole_D2.0mm | 1 | SWCLK test point | SWCLK
TP5 | Test Point | TP_NRST | TestPoint:TestPoint_Plated_Hole_D2.0mm | 1 | Reset test point | NRST
